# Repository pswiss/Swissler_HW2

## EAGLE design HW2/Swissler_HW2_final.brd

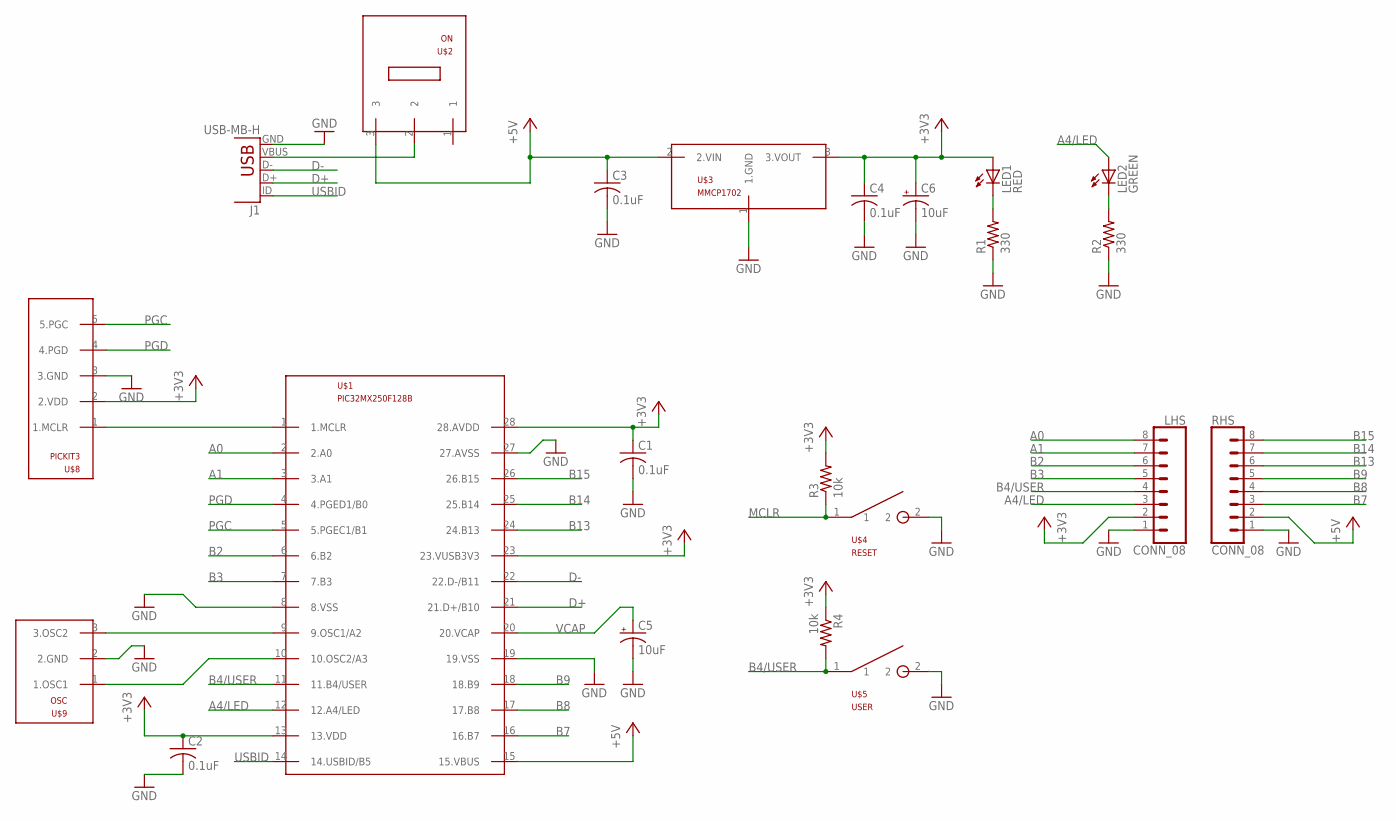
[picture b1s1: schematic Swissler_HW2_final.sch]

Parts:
C1, C2, C3, C4: 0.1uF; C025-025X050
C5, C6: 10uF; B45181B
J1: USB-MB-H
LED1: RED; LED3MM
LED2: GREEN; LED3MM
LHS: CONN_08; 1X08
R1, R2: 330; 0207/10
R3, R4: 10k; 0207/10
RHS: CONN_08; 1X08
U$1: PIC32MX250F128B; DIL28-3
U$2: ON; SLIDE
U$3: MMCP1702; TO92
U$4: RESET; PB
U$5: USER; PB
U$8: PICKIT3; 1X05
U$9: OSC

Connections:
+3V3: C1.1, C2.1, C4.1, C6.+, LED1.A, LHS.2, R3.2, R4.1, U$1.13 (13.VDD), U$1.23 (23.VUSB3V3), U$1.28 (28.AVDD), U$3.3 (3.VOUT), U$8.2 (2.VDD)
+5V: C3.1, RHS.2, U$1.15 (15.VBUS), U$2.3, U$3.2 (2.VIN)
A0: LHS.8, U$1.2 (2.A0)
A1: LHS.7, U$1.3 (3.A1)
A4/LED: LED2.A, LHS.3, U$1.12 (12.A4/LED)
B2: LHS.6, U$1.6 (6.B2)
B3: LHS.5, U$1.7 (7.B3)
B4/USER: LHS.4, R4.2, U$1.11 (11.B4/USER), U$5.1
B7: RHS.3, U$1.16 (16.B7)
B8: RHS.4, U$1.17 (17.B8)
B9: RHS.5, U$1.18 (18.B9)
B13: RHS.6, U$1.24 (24.B13)
B14: RHS.7, U$1.25 (25.B14)
B15: RHS.8, U$1.26 (26.B15)
D+: J1.D+, U$1.21 (21.D+/B10)
D-: J1.D-, U$1.22 (22.D-/B11)
GND: C1.2, C2.2, C3.2, C4.2, C5.-, C6.-, J1.GND, LHS.1, R1.1, R2.1, RHS.1, U$1.8 (8.VSS), U$1.19 (19.VSS), U$1.27 (27.AVSS), U$3.1 (1.GND), U$4.2, U$5.2, U$8.3 (3.GND), U$9.2 (2.GND)
MCLR: R3.1, U$1.1 (1.MCLR), U$4.1, U$8.1 (1.MCLR)
unnamed: LED2.K (C), R2.2
unnamed: LED1.K (C), R1.2
OSC1: U$1.9 (9.OSC1/A2), U$9.3 (3.OSC2)
OSC2: U$1.10 (10.OSC2/A3), U$9.1 (1.OSC1)
PGC: U$1.5 (5.PGEC1/B1), U$8.5 (5.PGC)
PGD: U$1.4 (4.PGED1/B0), U$8.4 (4.PGD)
USBID: J1.ID, U$1.14 (14.USBID/B5)
VBUS: J1.VBUS, U$2.2
VCAP: C5.+, U$1.20 (20.VCAP)

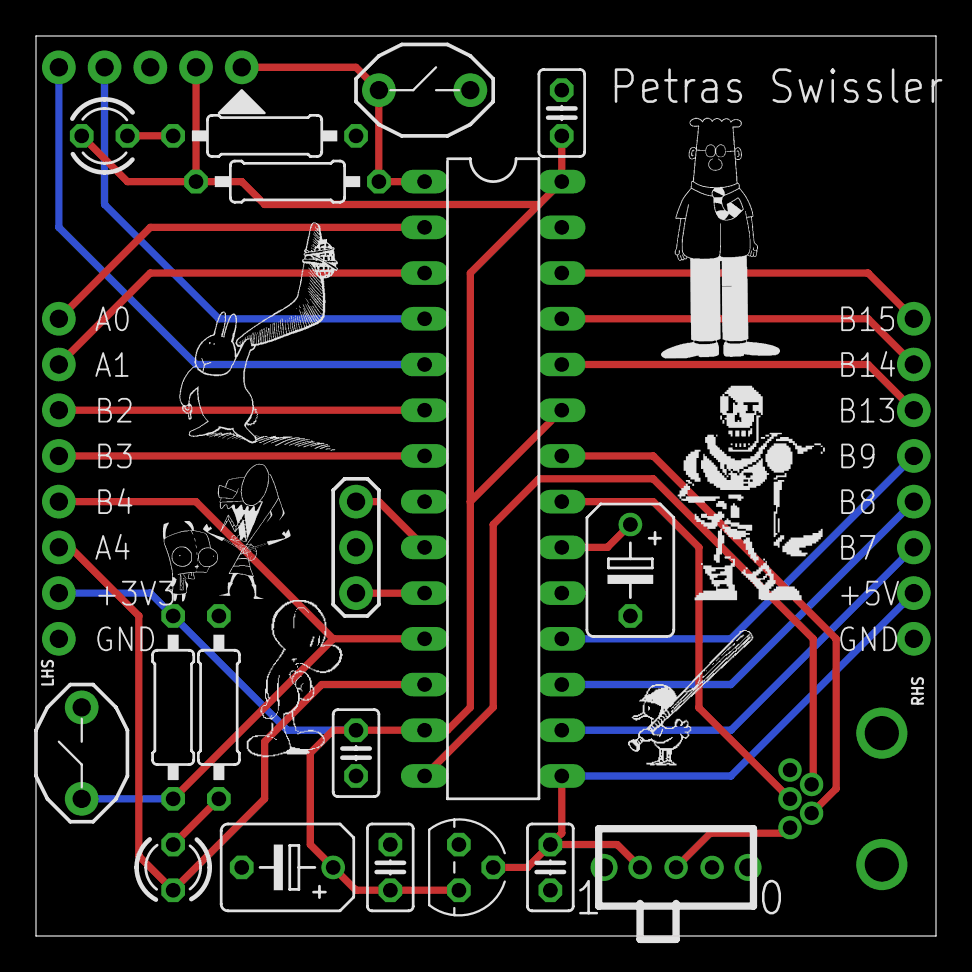
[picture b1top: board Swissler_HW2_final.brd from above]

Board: 2 copper layers, 50.0 x 50.0 mm, 22 parts (0 on the bottom side), 27 nets.

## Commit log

2017-04-02 :boom::camel: Added .gitattributes & .gitignore files
2017-04-04 Created Eagle File
2017-04-04 Halfway Through Creating Library
2017-04-04 Library Complete
2017-04-04 Schematic Started
2017-04-04 Schematic Complete
2017-04-04 Preliminary Board Layout
2017-04-04 Initial Board
2017-04-04 New Routing Approach
2017-04-04 Rev3
2017-04-05 Added Silkscreen images
2017-04-05 Smallupdate
2017-04-06 Finalized Everything
2017-04-06 Created Gerber Files
